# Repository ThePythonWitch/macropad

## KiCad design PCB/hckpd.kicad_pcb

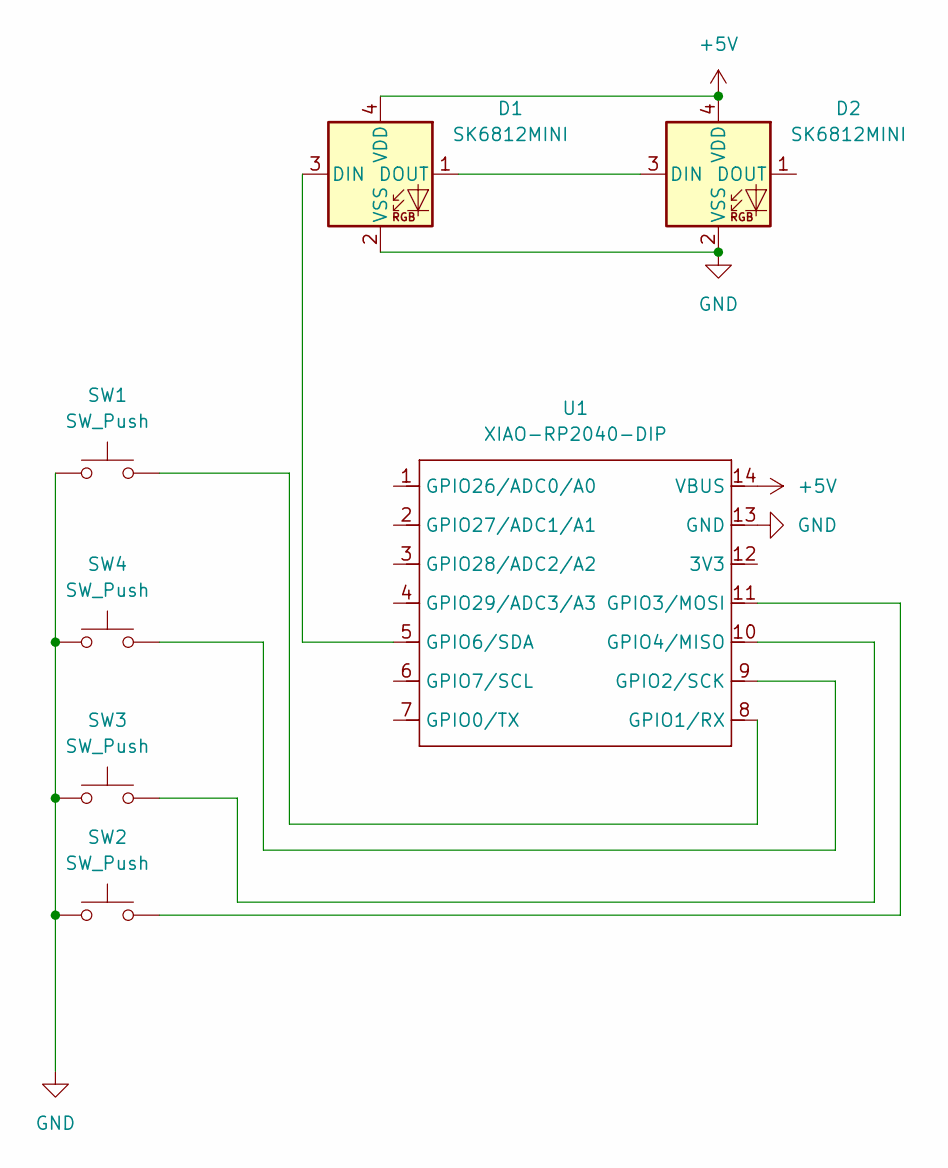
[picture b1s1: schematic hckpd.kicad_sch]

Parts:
D1, D2: SK6812MINI; LED_SK6812MINI_PLCC4_3.5x3.5mm_P1.75mm
SW1, SW2, SW3, SW4: SW_Push; SW_Cherry_MX_1.00u_PCB
U1: XIAO-RP2040-DIP

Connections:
+5V: D1.4 (VDD), D2.4 (VDD), U1.14 (VBUS)
GND: D1.2 (VSS), D2.2 (VSS), SW1.1, SW2.1, SW3.1, SW4.1, U1.13 (GND)
unnamed: D1.3 (DIN), U1.5 (GPIO6/SDA)
unnamed: D1.1 (DOUT), D2.3 (DIN)
unnamed: SW1.2, U1.8 (GPIO1/RX)
unnamed: SW4.2, U1.9 (GPIO2/SCK)
unnamed: SW2.2, U1.11 (GPIO3/MOSI)
unnamed: SW3.2, U1.10 (GPIO4/MISO)

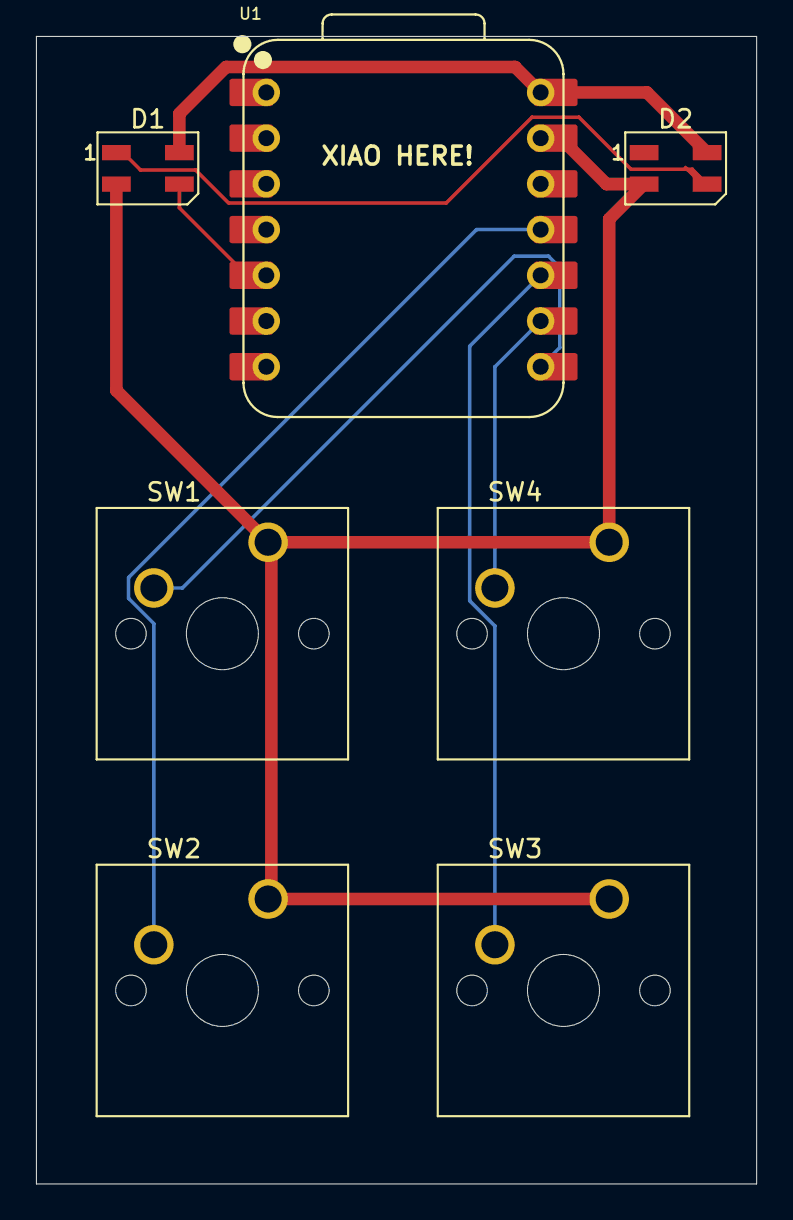
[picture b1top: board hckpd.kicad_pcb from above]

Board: 2 copper layers, 40.0 x 63.8 mm, 7 parts (0 on the bottom side), 8 nets.

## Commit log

2025-12-30 Add main.py firmware
2025-12-30 Add case STEP file
2025-12-30 Create case
2025-12-30 Add STEP files and other project assets
2025-12-30 Add STEP file
2025-12-30 Remove unwanted files from repo
2025-12-30 Organize KiCad project files into PCB folder
2025-12-30 Remove old hckpd folder after organizing PCB files
